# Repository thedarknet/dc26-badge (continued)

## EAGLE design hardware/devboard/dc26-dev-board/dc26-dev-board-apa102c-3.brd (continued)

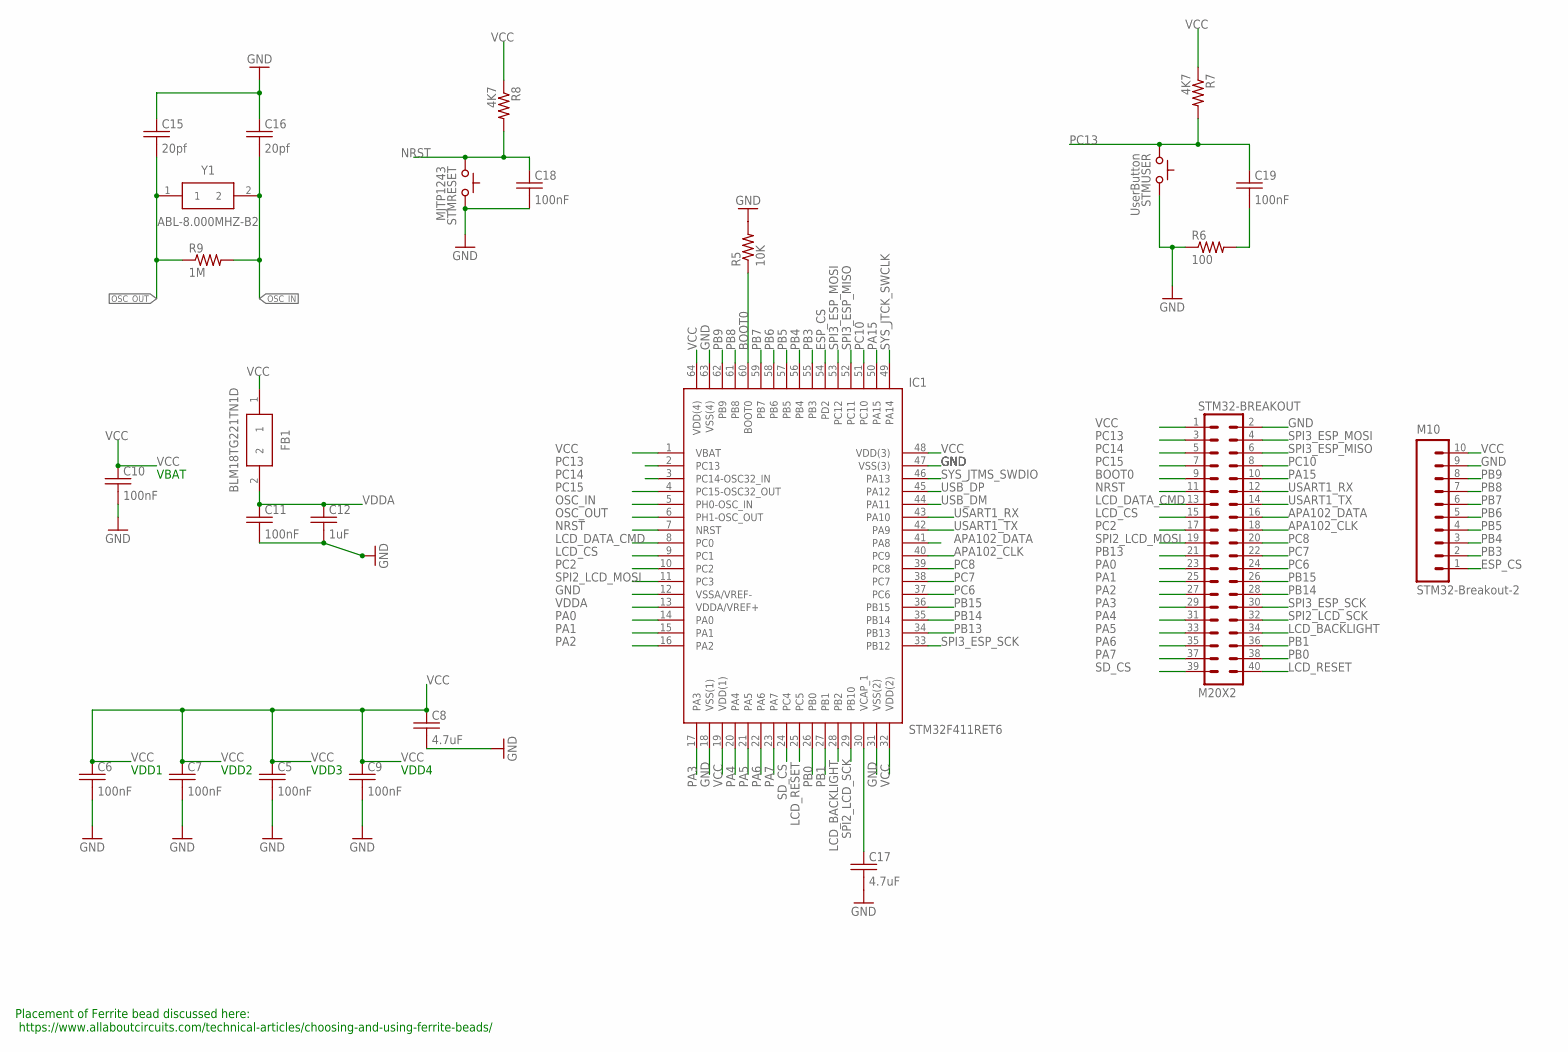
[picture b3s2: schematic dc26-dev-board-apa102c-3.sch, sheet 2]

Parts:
C5, C6, C7, C9, C10, C11, C18, C19: 100nF; C0805
C8, C17: 4.7uF; C0805
C12: 1uF; C0805
C15, C16: 20pf; C0805
FB1: BLM18TG221TN1D; BEADC1608X75N
IC1: STM32F411RET6; QFP50P1200X1200X160-64N
M10: STM32-Breakout-2; 1X10
R5: 10K; 0805
R6: 100; 0805
R7, R8: 4K7; 0805
R9: 1M; 0805
STM32-BREAKOUT: M20X2; 2X20
STMRESET: MJTP1243; TACTILE-2PIN-NARROW
STMUSER: UserButton; TACTILE-2PIN-NARROW
Y1: ABL-8.000MHZ-B2; HC/49US_(AT49)PTH

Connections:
APA102_CLK: IC1.40 (PC9), STM32-BREAKOUT.18; also elsewhere on the board
APA102_DATA: IC1.41 (PA8), STM32-BREAKOUT.16; also elsewhere on the board
BOOT0: IC1.60 (BOOT0), R5.1, STM32-BREAKOUT.9
ESP_CS: IC1.54 (PD2), M10.1; also elsewhere on the board
GND: C5.2, C6.2, C7.2, C8.2, C9.2, C10.2, C11.2, C12.2, C15.1, C16.1, C17.2, C18.2, IC1.12 (VSSA/VREF-), IC1.18 (VSS(1)), IC1.31 (VSS(2)), IC1.47 (VSS(3)), IC1.63 (VSS(4)), M10.9, R5.2, R6.1, STM32-BREAKOUT.2, STMRESET.P$1 (A), STMUSER.P$1 (A); also elsewhere on the board
LCD_BACKLIGHT: IC1.28 (PB2), STM32-BREAKOUT.34; also elsewhere on the board
LCD_CS: IC1.9 (PC1), STM32-BREAKOUT.15; also elsewhere on the board
LCD_DATA_CMD: IC1.8 (PC0), STM32-BREAKOUT.13; also elsewhere on the board
LCD_RESET: IC1.25 (PC5), STM32-BREAKOUT.40; also elsewhere on the board
unnamed: C19.2, R6.2
unnamed: C17.1, IC1.30 (VCAP_1)
NRST: C18.1, IC1.7 (NRST), R8.2, STM32-BREAKOUT.11, STMRESET.P$2 (C)
OSC_IN: C16.2, IC1.5 (PH0-OSC_IN), R9.2, Y1.2
OSC_OUT: C15.2, IC1.6 (PH1-OSC_OUT), R9.1, Y1.1
PA0: IC1.14 (PA0), STM32-BREAKOUT.23
PA1: IC1.15 (PA1), STM32-BREAKOUT.25
PA2: IC1.16 (PA2), STM32-BREAKOUT.27
PA3: IC1.17 (PA3), STM32-BREAKOUT.29
PA4: IC1.20 (PA4), STM32-BREAKOUT.31
PA5: IC1.21 (PA5), STM32-BREAKOUT.33
PA6: IC1.22 (PA6), STM32-BREAKOUT.35
PA7: IC1.23 (PA7), STM32-BREAKOUT.37
PA15: IC1.50 (PA15), STM32-BREAKOUT.10
PB0: IC1.26 (PB0), STM32-BREAKOUT.38
PB1: IC1.27 (PB1), STM32-BREAKOUT.36
PB3: IC1.55 (PB3), M10.2
PB4: IC1.56 (PB4), M10.3
PB5: IC1.57 (PB5), M10.4
PB6: IC1.58 (PB6), M10.5
PB7: IC1.59 (PB7), M10.6
PB8: IC1.61 (PB8), M10.7
PB9: IC1.62 (PB9), M10.8
PB13: IC1.34 (PB13), STM32-BREAKOUT.21
PB14: IC1.35 (PB14), STM32-BREAKOUT.28
PB15: IC1.36 (PB15), STM32-BREAKOUT.26
PC2: IC1.10 (PC2), STM32-BREAKOUT.17
PC6: IC1.37 (PC6), STM32-BREAKOUT.24
PC7: IC1.38 (PC7), STM32-BREAKOUT.22
PC8: IC1.39 (PC8), STM32-BREAKOUT.20
PC10: IC1.51 (PC10), STM32-BREAKOUT.8
PC13: C19.1, IC1.2 (PC13), R7.2, STM32-BREAKOUT.3, STMUSER.P$2 (C)
PC14: IC1.3 (PC14-OSC32_IN), STM32-BREAKOUT.5
PC15: IC1.4 (PC15-OSC32_OUT), STM32-BREAKOUT.7
SD_CS: IC1.24 (PC4), STM32-BREAKOUT.39; also elsewhere on the board
SPI2_LCD_MOSI: IC1.11 (PC3), STM32-BREAKOUT.19; also elsewhere on the board
SPI2_LCD_SCK: IC1.29 (PB10), STM32-BREAKOUT.32; also elsewhere on the board
SPI3_ESP_MISO: IC1.52 (PC11), STM32-BREAKOUT.6; also elsewhere on the board
SPI3_ESP_MOSI: IC1.53 (PC12), STM32-BREAKOUT.4; also elsewhere on the board
SPI3_ESP_SCK: IC1.33 (PB12), STM32-BREAKOUT.30; also elsewhere on the board
SYS_JTCK_SWCLK: IC1.49 (PA14); also elsewhere on the board
SYS_JTMS_SWDIO: IC1.46 (PA13); also elsewhere on the board
USART1_RX: IC1.43 (PA10), STM32-BREAKOUT.12
USART1_TX: IC1.42 (PA9), STM32-BREAKOUT.14
USB_DM: IC1.44 (PA11); also elsewhere on the board
USB_DP: IC1.45 (PA12); also elsewhere on the board
VCC: C5.1, C6.1, C7.1, C8.1, C9.1, C10.1, FB1.1, IC1.1 (VBAT), IC1.19 (VDD(1)), IC1.32 (VDD(2)), IC1.48 (VDD(3)), IC1.64 (VDD(4)), M10.10, R7.1, R8.1, STM32-BREAKOUT.1; also elsewhere on the board
VDDA: C11.1, C12.1, FB1.2, IC1.13 (VDDA/VREF+)

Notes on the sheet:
Placement of Ferrite bead discussed here: https://www.allaboutcircuits.com/technical-articles/choosing-and-using-ferrite-beads/
VBAT
VDD1
VDD2
VDD3
VDD4

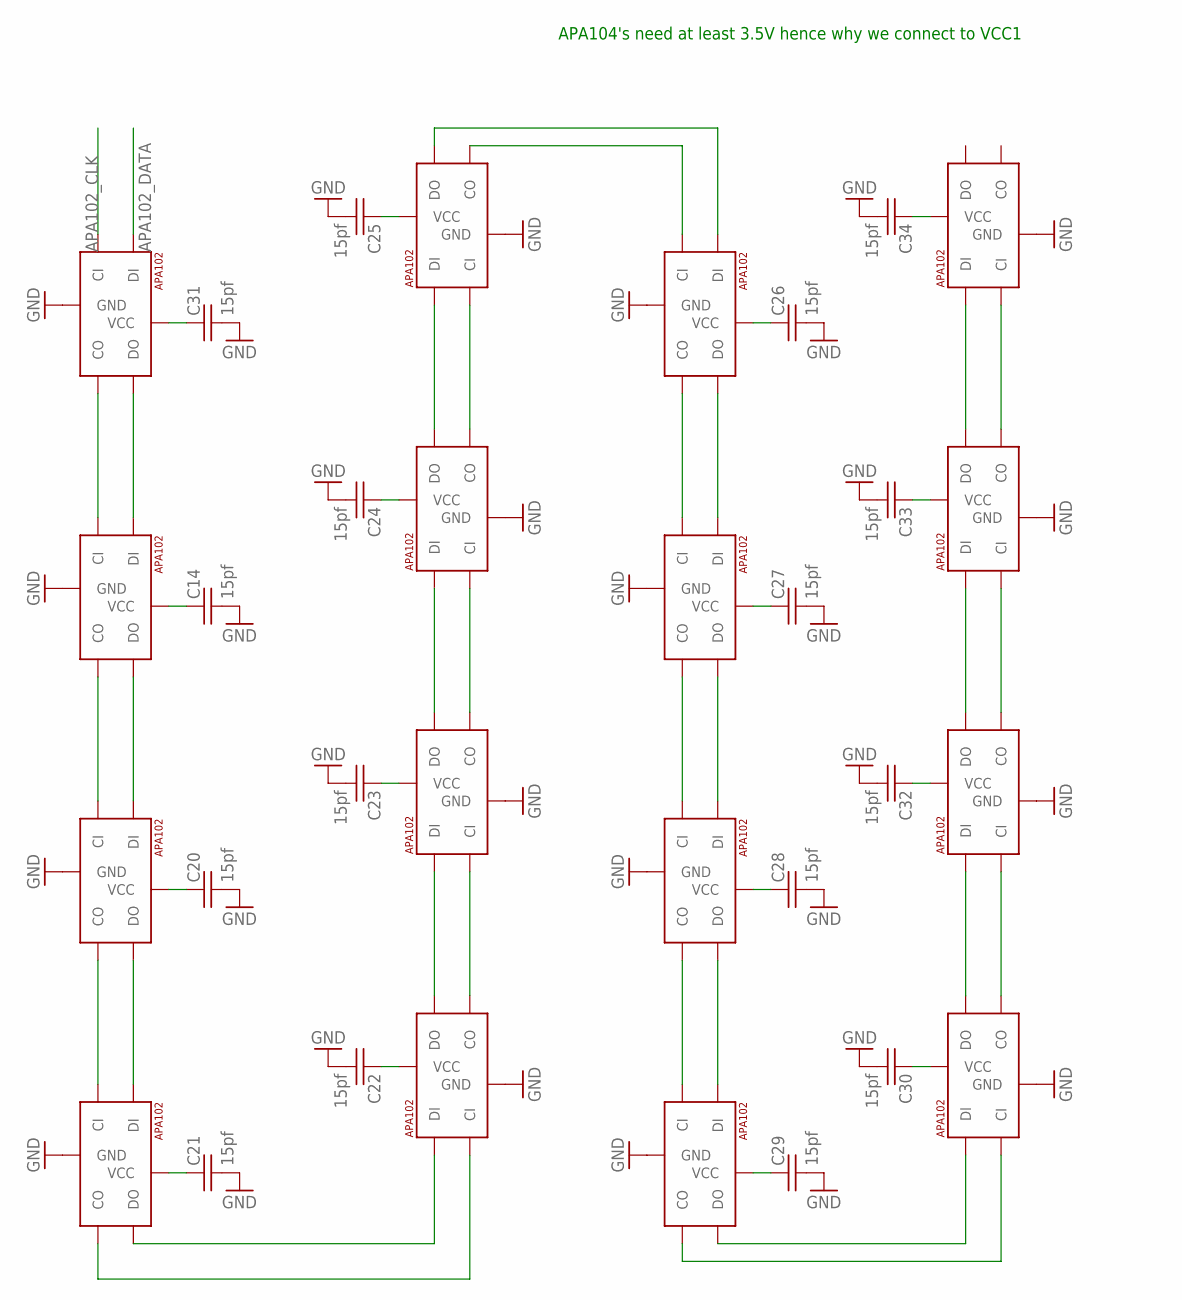
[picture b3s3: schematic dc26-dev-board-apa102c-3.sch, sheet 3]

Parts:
C14, C20, C21, C22, C23, C24, C25, C26, C27, C28, C29, C30, C31, C32, C33, C34: 15pf; C0805
U$5, U$6, U$7, U$8, U$9, U$10, U$11, U$12, U$13, U$14, U$15, U$16, U$17, U$18, U$19, U$20: APA1025050; APA102_5050

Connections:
APA102_CLK: U$8.5 (CI); also elsewhere on the board
APA102_DATA: U$8.4 (DI); also elsewhere on the board
GND: C14.2, C20.2, C21.2, C22.2, C23.2, C24.2, C25.2, C26.2, C27.2, C28.2, C29.2, C30.2, C31.2, C32.2, C33.2, C34.2, U$5.6 (GND), U$6.6 (GND), U$7.6 (GND), U$8.6 (GND), U$9.6 (GND), U$10.6 (GND), U$11.6 (GND), U$12.6 (GND), U$13.6 (GND), U$14.6 (GND), U$15.6 (GND), U$16.6 (GND), U$17.6 (GND), U$18.6 (GND), U$19.6 (GND), U$20.6 (GND); also elsewhere on the board
unnamed: U$5.5 (CI), U$8.2 (CO)
unnamed: U$5.2 (CO), U$6.5 (CI)
unnamed: U$6.2 (CO), U$7.5 (CI)
unnamed: U$6.3 (DO), U$7.4 (DI)
unnamed: U$5.3 (DO), U$6.4 (DI)
unnamed: U$5.4 (DI), U$8.3 (DO)
unnamed: U$7.3 (DO), U$9.4 (DI)
unnamed: U$7.2 (CO), U$9.5 (CI)
unnamed: U$9.2 (CO), U$10.5 (CI)
unnamed: U$9.3 (DO), U$10.4 (DI)
unnamed: U$10.2 (CO), U$11.5 (CI)
unnamed: U$10.3 (DO), U$11.4 (DI)
unnamed: U$11.2 (CO), U$12.5 (CI)
unnamed: U$11.3 (DO), U$12.4 (DI)
unnamed: U$12.2 (CO), U$13.5 (CI)
unnamed: U$12.3 (DO), U$13.4 (DI)
unnamed: U$13.2 (CO), U$14.5 (CI)
unnamed: U$13.3 (DO), U$14.4 (DI)
unnamed: U$14.2 (CO), U$15.5 (CI)
unnamed: U$14.3 (DO), U$15.4 (DI)
unnamed: U$15.2 (CO), U$16.5 (CI)
unnamed: U$15.3 (DO), U$16.4 (DI)
unnamed: U$16.3 (DO), U$17.4 (DI)
unnamed: U$16.2 (CO), U$17.5 (CI)
unnamed: U$17.3 (DO), U$18.4 (DI)
unnamed: U$17.2 (CO), U$18.5 (CI)
unnamed: U$18.2 (CO), U$19.5 (CI)
unnamed: U$18.3 (DO), U$19.4 (DI)
unnamed: U$19.2 (CO), U$20.5 (CI)
unnamed: U$19.3 (DO), U$20.4 (DI)
VIN: C14.1, C20.1, C21.1, C22.1, C23.1, C24.1, C25.1, C26.1, C27.1, C28.1, C29.1, C30.1, C31.1, C32.1, C33.1, C34.1, U$5.1 (VCC), U$6.1 (VCC), U$7.1 (VCC), U$8.1 (VCC), U$9.1 (VCC), U$10.1 (VCC), U$11.1 (VCC), U$12.1 (VCC), U$13.1 (VCC), U$14.1 (VCC), U$15.1 (VCC), U$16.1 (VCC), U$17.1 (VCC), U$18.1 (VCC), U$19.1 (VCC), U$20.1 (VCC); also elsewhere on the board

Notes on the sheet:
APA104's need at least 3.5V hence why we connect to VCC1

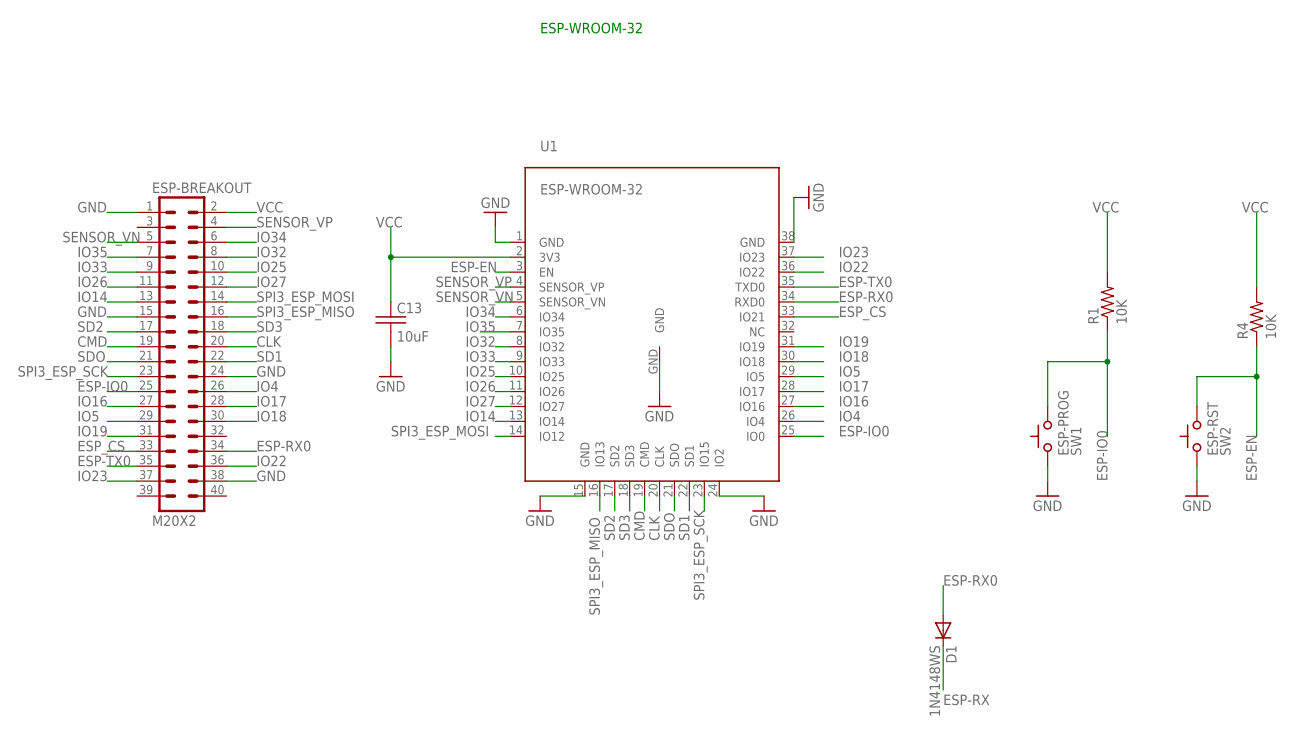
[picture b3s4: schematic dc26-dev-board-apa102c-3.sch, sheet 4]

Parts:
C13: 10uF; C0805
D1: 1N4148WS; SOD-323
ESP-BREAKOUT: M20X2; 2X20
ESP-PROG: SW1; TACTILE-2PIN-NARROW
ESP-RST: SW2; TACTILE-2PIN-NARROW
R1, R4: 10K; 0805
U1: ESP-WROOM-32

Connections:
CLK: ESP-BREAKOUT.20, U1.20 (CLK)
CMD: ESP-BREAKOUT.19, U1.19 (CMD)
ESP-EN: ESP-RST.P$1 (A), R4.1, U1.3 (EN)
ESP-IO0: ESP-BREAKOUT.25, ESP-PROG.P$1 (A), R1.1, U1.25 (IO0)
ESP-RX: D1.1 (C); also elsewhere on the board
ESP-RX0: D1.2 (A), ESP-BREAKOUT.34, U1.34 (RXD0)
ESP-TX0: ESP-BREAKOUT.35, U1.35 (TXD0); also elsewhere on the board
ESP_CS: ESP-BREAKOUT.33, U1.33 (IO21); also elsewhere on the board
GND: C13.2, ESP-BREAKOUT.1, ESP-BREAKOUT.15, ESP-BREAKOUT.24, ESP-BREAKOUT.38, ESP-PROG.P$2 (C), ESP-RST.P$2 (C), U1.1 (GND), U1.15 (GND), U1.24 (IO2), U1.38 (GND), U1.GND; also elsewhere on the board
IO4: ESP-BREAKOUT.26, U1.26 (IO4)
IO5: ESP-BREAKOUT.29, U1.29 (IO5)
IO14: ESP-BREAKOUT.13, U1.13 (IO14)
IO16: ESP-BREAKOUT.27, U1.27 (IO16)
IO17: ESP-BREAKOUT.28, U1.28 (IO17)
IO18: ESP-BREAKOUT.30, U1.30 (IO18)
IO19: ESP-BREAKOUT.31, U1.31 (IO19)
IO22: ESP-BREAKOUT.36, U1.36 (IO22)
IO23: ESP-BREAKOUT.37, U1.37 (IO23)
IO25: ESP-BREAKOUT.10, U1.10 (IO25)
IO26: ESP-BREAKOUT.11, U1.11 (IO26)
IO27: ESP-BREAKOUT.12, U1.12 (IO27)
IO32: ESP-BREAKOUT.8, U1.8 (IO32)
IO33: ESP-BREAKOUT.9, U1.9 (IO33)
IO34: ESP-BREAKOUT.6, U1.6 (IO34)
IO35: ESP-BREAKOUT.7, U1.7 (IO35)
SD1: ESP-BREAKOUT.22, U1.22 (SD1)
SD2: ESP-BREAKOUT.17, U1.17 (SD2)
SD3: ESP-BREAKOUT.18, U1.18 (SD3)
SDO: ESP-BREAKOUT.21, U1.21 (SDO)
SENSOR_VN: ESP-BREAKOUT.5, U1.5 (SENSOR_VN)
SENSOR_VP: ESP-BREAKOUT.4, U1.4 (SENSOR_VP)
SPI3_ESP_MISO: ESP-BREAKOUT.16, U1.16 (IO13); also elsewhere on the board
SPI3_ESP_MOSI: ESP-BREAKOUT.14, U1.14 (IO12); also elsewhere on the board
SPI3_ESP_SCK: ESP-BREAKOUT.23, U1.23 (IO15); also elsewhere on the board
VCC: C13.1, ESP-BREAKOUT.2, R1.2, R4.2, U1.2 (3V3); also elsewhere on the board

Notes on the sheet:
ESP-WROOM-32

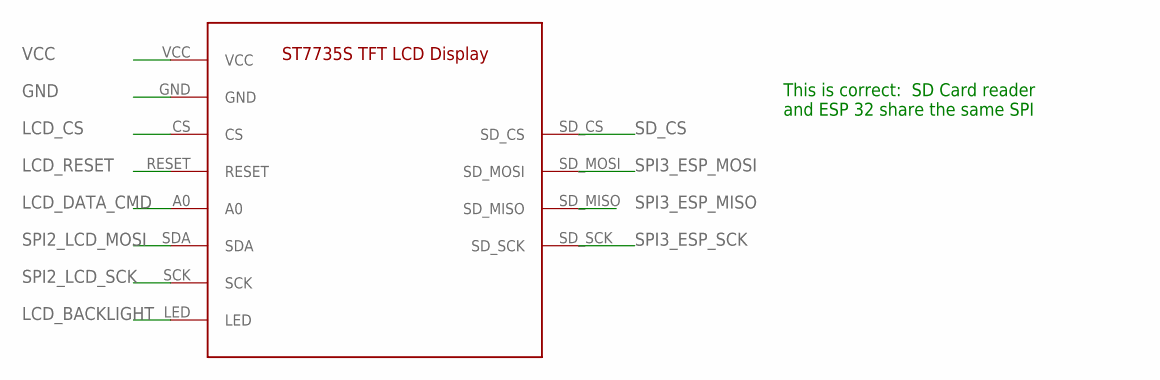
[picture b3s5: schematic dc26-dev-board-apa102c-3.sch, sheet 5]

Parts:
U$1: ST7735S_LCD_MODULE; ST7735S_LCD_DISPLAY

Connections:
GND: U$1.GND; also elsewhere on the board
LCD_BACKLIGHT: U$1.LED; also elsewhere on the board
LCD_CS: U$1.CS; also elsewhere on the board
LCD_DATA_CMD: U$1.A0; also elsewhere on the board
LCD_RESET: U$1.RESET; also elsewhere on the board
SD_CS: U$1.SD_CS; also elsewhere on the board
SPI2_LCD_MOSI: U$1.SDA; also elsewhere on the board
SPI2_LCD_SCK: U$1.SCK; also elsewhere on the board
SPI3_ESP_MISO: U$1.SD_MISO; also elsewhere on the board
SPI3_ESP_MOSI: U$1.SD_MOSI; also elsewhere on the board
SPI3_ESP_SCK: U$1.SD_SCK; also elsewhere on the board
VCC: U$1.VCC; also elsewhere on the board

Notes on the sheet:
This is correct: SD Card reader and ESP 32 share the same SPI

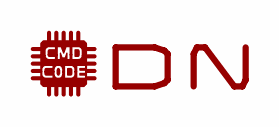
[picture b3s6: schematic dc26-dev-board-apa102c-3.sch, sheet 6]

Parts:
U$2: CMD_C0DE_LOGO
U$3: DARKNET_DD; DARKNET_D
U$4: DARKNET_NN; DARKNET_N

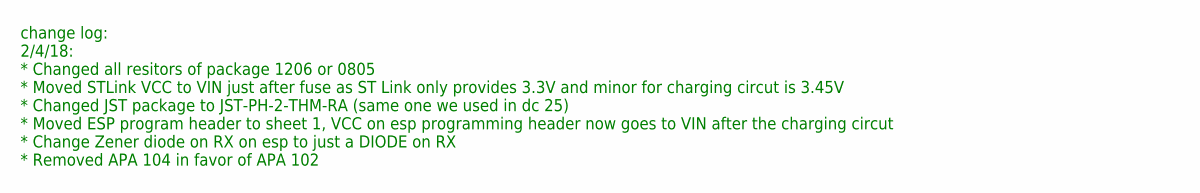
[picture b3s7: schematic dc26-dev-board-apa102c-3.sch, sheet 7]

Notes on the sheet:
change log: 2/4/18: * Changed all resitors of package 1206 or 0805 * Moved STLink VCC to VIN just after fuse as ST Link only provides 3.3V and minor for charging circut is 3.45V * Changed JST package to JST-PH-2-THM-RA (same one we used in dc 25) * Moved ESP program header to sheet 1, VCC on esp pr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

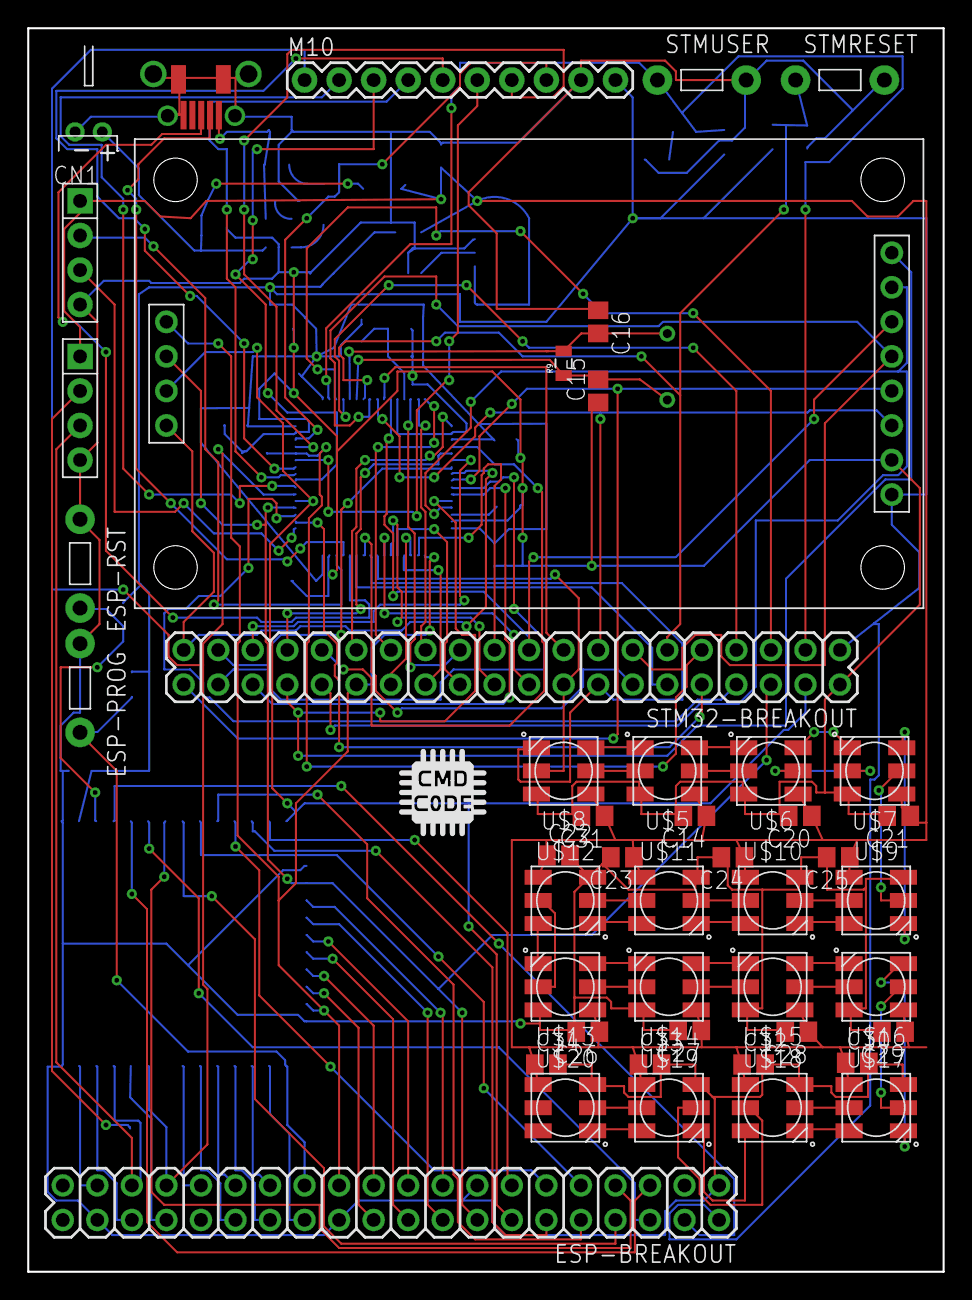
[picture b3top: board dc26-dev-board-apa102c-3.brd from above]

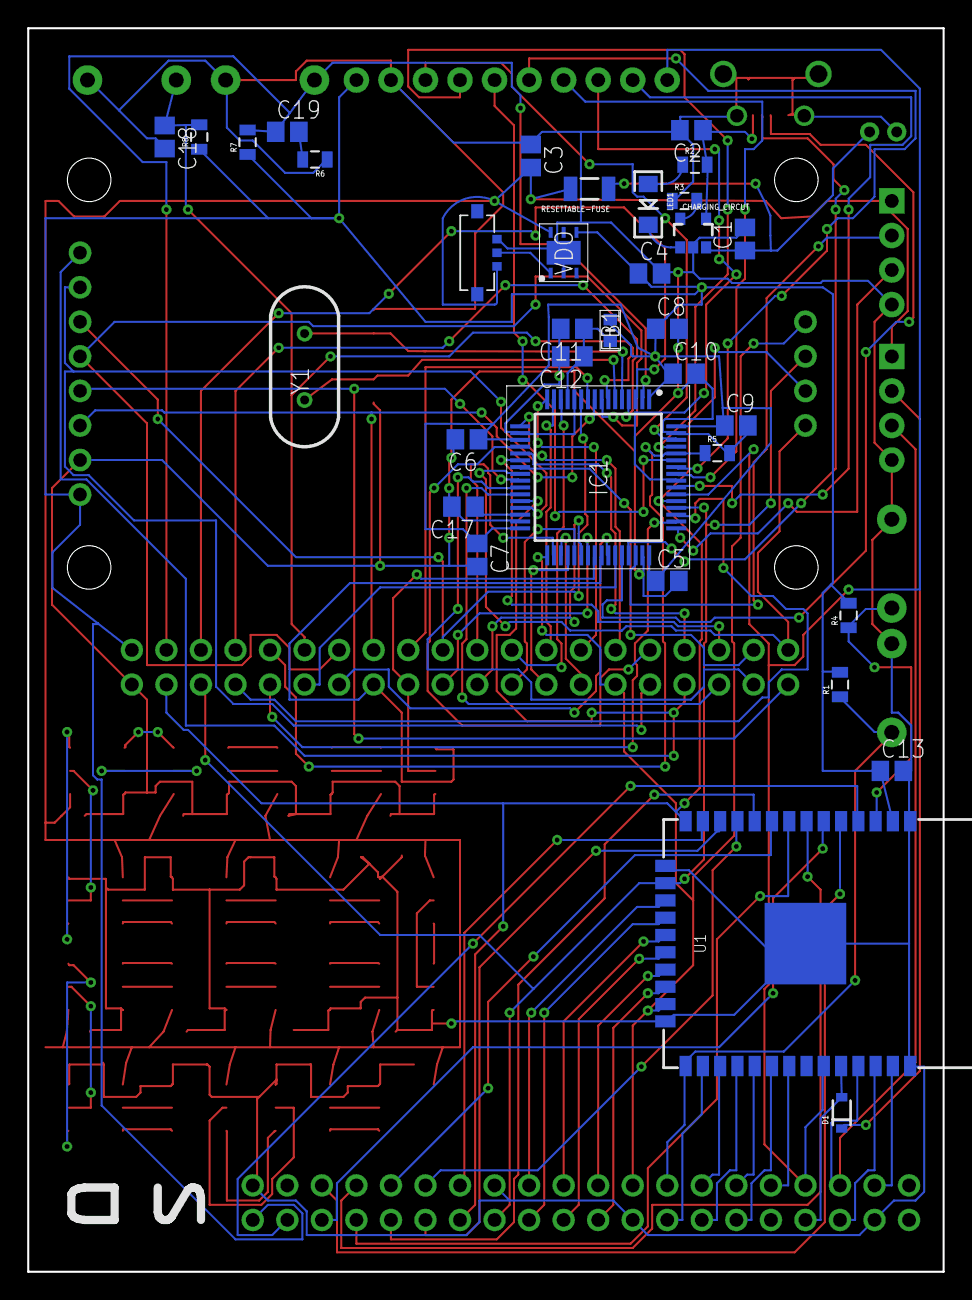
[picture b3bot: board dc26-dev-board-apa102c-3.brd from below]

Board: 2 copper layers, 67.3 x 91.4 mm, 84 parts (34 on the bottom side), 123 nets.

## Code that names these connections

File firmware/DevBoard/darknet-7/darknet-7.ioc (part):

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Mcu.Name=STM32F411R(C-E)Tx
Mcu.Package=LQFP64
Mcu.UserName=STM32F411RETx
PA10.GPIOParameters=GPIO_Label
PA10.GPIO_Label=USART1_RX_TO_ESP_TX_PIN_4
PA10.Mode=Asynchronous
PA10.Signal=USART1_RX
PA11.Mode=Device_Only
PA11.Signal=USB_OTG_FS_DM
PA12.Mode=Device_Only
PA12.Signal=USB_OTG_FS_DP
PA13.Mode=Serial_Wire
PA13.Signal=SYS_JTMS-SWDIO
PA14.Mode=Serial_Wire
PA14.Signal=SYS_JTCK-SWCLK
PA2.Mode=Asynchronous
PA2.Signal=USART2_TX
PA3.Mode=Asynchronous
PA3.Signal=USART2_RX
PA8.GPIOParameters=GPIO_Label
PA8.GPIO_Label=SHITTY_ADD_ON_BADGE_I2C_SCL
PA8.Mode=I2C
PA8.Signal=I2C3_SCL
PA9.GPIOParameters=GPIO_Label
PA9.GPIO_Label=USART1_TX_TO_ESP_RX_PIN_5
PA9.Mode=Asynchronous
PA9.Signal=USART1_TX
PB10.GPIOParameters=GPIO_Label
PB10.GPIO_Label=SPI2_LCD_SCK
PB10.Mode=Simplex_Bidirectional_Master
PB10.Signal=SPI2_SCK
PB12.GPIOParameters=GPIO_Label
PB12.GPIO_Label=SPI3_SD_SCK
PB12.Mode=Full_Duplex_Master
PB12.Signal=SPI3_SCK
PB2.GPIOParameters=GPIO_Label
PB2.GPIO_Label=LCD_BACKLIGHT
PB2.Signal=GPIO_Output
PB4.GPIOParameters=GPIO_Label
PB4.GPIO_Label=SHITTY_ADD_ON_BADGE_I2C_SDA
PB4.Mode=I2C
PB4.Signal=I2C3_SDA
PB6.GPIOParameters=GPIO_Label
PB6.GPIO_Label=ESP_I2C1_SCL
PB6.Mode=I2C
PB6.Signal=I2C1_SCL
PB7.GPIOParameters=GPIO_Label
PB7.GPIO_Label=ESP_I2C1_SDA
PB7.Mode=I2C
PB7.Signal=I2C1_SDA
PB8.GPIOParameters=GPIO_Label
PB8.GPIO_Label=BUTTON_UP
PB8.Signal=GPIO_Input
PB9.GPIOParameters=GPIO_Label
PB9.GPIO_Label=BUTTON_DOWN
PB9.Signal=GPIO_Input
PC0.GPIOParameters=GPIO_Label
PC0.GPIO_Label=LCD_DATA_CMD
PC0.Signal=GPIO_Output
PC1.GPIOParameters=GPIO_Label
PC1.GPIO_Label=LCD_CS
PC1.Signal=GPIO_Output
PC10.GPIOParameters=GPIO_Label
PC10.GPIO_Label=SIMPLE_LED1
PC10.Signal=GPIO_Output
PC11.GPIOParameters=GPIO_Label
PC11.GPIO_Label=SPI3_SD_MISO
PC11.Mode=Full_Duplex_Master
PC11.Signal=SPI3_MISO
PC12.GPIOParameters=GPIO_Label
PC12.GPIO_Label=SPI3_SD_MOSI
PC12.Mode=Full_Duplex_Master
PC12.Signal=SPI3_MOSI
PC13-ANTI_TAMP.GPIOParameters=GPIO_Label
PC13-ANTI_TAMP.GPIO_Label=MID_BUTTON1
PC13-ANTI_TAMP.Signal=GPIO_Input
PC14-OSC32_IN.GPIOParameters=GPIO_Label
PC14-OSC32_IN.GPIO_Label=BUTTON_RIGHT
PC14-OSC32_IN.Signal=GPIO_Input
PC15-OSC32_OUT.GPIOParameters=GPIO_Label
PC15-OSC32_OUT.GPIO_Label=BUTTON_FIRE1
PC15-OSC32_OUT.Signal=GPIO_Input
PC2.GPIOParameters=GPIO_Label
PC2.GPIO_Label=BUTTON_LEFT
PC2.Signal=GPIO_Input
PC3.GPIOParameters=GPIO_Label
PC3.GPIO_Label=SPI2_LCD_MOSI
PC3.Mode=Simplex_Bidirectional_Master
PC3.Signal=SPI2_MOSI
PC4.GPIOParameters=GPIO_Label
PC4.GPIO_Label=SD_CS
PC4.Signal=GPIO_Output
PC5.GPIOParameters=GPIO_Label
PC5.GPIO_Label=LCD_RESET
PC5.Signal=GPIO_Output
PC7.GPIOParameters=GPIO_Speed,GPIO_Label
PC7.GPIO_Label=GPIO_APA106_DATA
PC7.GPIO_Speed=GPIO_SPEED_FREQ_MEDIUM
PC7.Signal=GPIO_Output
PC8.GPIOParameters=GPIO_Label
PC8.GPIO_Label=GPIO_APA102_DATA
PC8.Signal=GPIO_Output
PC9.GPIOParameters=GPIO_Speed,GPIO_PuPd,GPIO_Label
PC9.GPIO_Label=TIM_APA102_CLK
PC9.GPIO_PuPd=GPIO_PULLUP
PC9.GPIO_Speed=GPIO_SPEED_FREQ_HIGH
PC9.Signal=S_TIM3_CH4
PD2.GPIOParameters=GPIO_Label
PD2.GPIO_Label=ESP_INTER
PD2.Signal=GPXTI2
PH0\ -\ OSC_IN.Mode=HSE-External-Oscillator
PH0\ -\ OSC_IN.Signal=RCC_OSC_IN
PH1\ -\ OSC_OUT.Mode=HSE-External-Oscillator
PH1\ -\ OSC_OUT.Signal=RCC_OSC_OUT
RCC.HSE_VALUE=8000000
RCC.SYSCLKFreq_VALUE=96000000.00000001
RCC.SYSCLKSource=RCC_SYSCLKSOURCE_PLLCLK
board=darknet-7

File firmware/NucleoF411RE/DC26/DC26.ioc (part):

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Mcu.Name=STM32F411R(C-E)Tx
Mcu.Package=LQFP64
Mcu.UserName=STM32F411RETx
PA10.Mode=Asynchronous
PA10.Signal=USART1_RX
PA11.Mode=Device_Only
PA11.Signal=USB_OTG_FS_DM
PA12.Mode=Device_Only
PA12.Signal=USB_OTG_FS_DP
PA13.GPIOParameters=GPIO_Label
PA13.GPIO_Label=TMS
PA13.Mode=Serial_Wire
PA13.Signal=SYS_JTMS-SWDIO
PA14.GPIOParameters=GPIO_Label
PA14.GPIO_Label=TCK
PA14.Mode=Serial_Wire
PA14.Signal=SYS_JTCK-SWCLK
PA2.GPIOParameters=GPIO_Label
PA2.GPIO_Label=USART_TX
PA2.Signal=USART2_TX
PA3.GPIOParameters=GPIO_Label
PA3.GPIO_Label=USART_RX
PA3.Signal=USART2_RX
PA5.GPIOParameters=GPIO_Label
PA5.GPIO_Label=LD2 [Green Led]
PA5.Signal=GPIO_Output
PA9.Mode=Asynchronous
PA9.Signal=USART1_TX
PB10.GPIOParameters=GPIO_Label
PB10.GPIO_Label=SPI2_LCD_SCK
PB10.Mode=Simplex_Bidirectional_Master
PB10.Signal=SPI2_SCK
PB12.GPIOParameters=GPIO_Label
PB12.GPIO_Label=SPI3_ESP_SCK
PB12.Mode=Full_Duplex_Master
PB12.Signal=SPI3_SCK
PB2.GPIOParameters=GPIO_Label
PB2.GPIO_Label=LCD_BACKLIGHT
PB2.Signal=GPIO_Output
PB3.GPIOParameters=GPIO_Label
PB3.GPIO_Label=SWO
PB3.Signal=SYS_JTDO-SWO
PB6.Mode=I2C
PB6.Signal=I2C1_SCL
PB7.Mode=I2C
PB7.Signal=I2C1_SDA
PC0.GPIOParameters=GPIO_Label
PC0.GPIO_Label=LCD_DATA_CMD
PC0.Signal=GPIO_Output
PC1.GPIOParameters=GPIO_Label
PC1.GPIO_Label=LCD_CS
PC1.Signal=GPIO_Output
PC11.GPIOParameters=GPIO_Label
PC11.GPIO_Label=SPI3_ESP_MISO
PC11.Mode=Full_Duplex_Master
PC11.Signal=SPI3_MISO
PC12.GPIOParameters=GPIO_Label
PC12.GPIO_Label=SPI3_ESP_MOSI
PC12.Mode=Full_Duplex_Master
PC12.Signal=SPI3_MOSI
PC13-ANTI_TAMP.GPIOParameters=GPIO_Label,GPIO_ModeDefaultEXTI
PC13-ANTI_TAMP.GPIO_Label=B1 [Blue PushButton]
PC13-ANTI_TAMP.GPIO_ModeDefaultEXTI=GPIO_MODE_IT_FALLING
PC13-ANTI_TAMP.Signal=GPXTI13
PC14-OSC32_IN.Signal=RCC_OSC32_IN
PC15-OSC32_OUT.Signal=RCC_OSC32_OUT
PC3.GPIOParameters=GPIO_Label
PC3.GPIO_Label=SPI2_LCD_MOSI
PC3.Mode=Simplex_Bidirectional_Master
PC3.Signal=SPI2_MOSI
PC4.GPIOParameters=GPIO_Label
PC4.GPIO_Label=SD_CS
PC4.Signal=GPIO_Output
PC5.GPIOParameters=GPIO_Label
PC5.GPIO_Label=LCD_RESET
PC5.Signal=GPIO_Output
PC8.GPIOParameters=GPIO_Speed,GPIO_Label
PC8.GPIO_Label=GPIO_APA104_DATA
PC8.GPIO_Speed=GPIO_SPEED_FREQ_HIGH
PC8.Signal=GPIO_Output
PD2.GPIOParameters=GPIO_Speed,PinState,GPIO_Label
PD2.GPIO_Label=ESP_CS
PD2.GPIO_Speed=GPIO_SPEED_FREQ_MEDIUM
PD2.PinState=GPIO_PIN_RESET
PD2.Signal=GPIO_Output
PH0\ -\ OSC_IN.Mode=HSE-External-Oscillator
PH0\ -\ OSC_IN.Signal=RCC_OSC_IN
PH1\ -\ OSC_OUT.Mode=HSE-External-Oscillator
PH1\ -\ OSC_OUT.Signal=RCC_OSC_OUT
RCC.HSE_VALUE=8000000
RCC.SYSCLKFreq_VALUE=96000000.00000001
RCC.SYSCLKSource=RCC_SYSCLKSOURCE_PLLCLK
board=NUCLEO-F411RE
boardIOC=true

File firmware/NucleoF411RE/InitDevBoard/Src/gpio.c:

/**
  ******************************************************************************
  * File Name          : gpio.c
  * Description        : This file provides code for the configuration
  *                      of all used GPIO pins.
  ******************************************************************************
  * This notice applies to any and all portions of this file
  * that are not between comment pairs USER CODE BEGIN and
  * USER CODE END. Other portions of this file, whether 
  * inserted by the user or by software development tools
  * are owned by their respective copyright owners.
  *
  * Copyright (c) 2017 STMicroelectronics International N.V. 
  * All rights reserved.
  *
  * Redistribution and use in source and binary forms, with or without 
  * modification, are permitted, provided that the following conditions are met:
  *
  * 1. Redistribution of source code must retain the above copyright notice, 
  *    this list of conditions and the following disclaimer.
  * 2. Redistributions in binary form must reproduce the above copyright notice,
  *    this list of conditions and the following disclaimer in the documentation
  *    and/or other materials provided with the distribution.
  * 3. Neither the name of STMicroelectronics nor the names of other 
  *    contributors to this software may be used to endorse or promote products 
  *    derived from this software without specific written permission.
  * 4. This software, including modifications and/or derivative works of this 
  *    software, must execute solely and exclusively on microcontroller or
  *    microprocessor devices manufactured by or for STMicroelectronics.
  * 5. Redistribution and use of this software other than as permitted under 
  *    this license is void and will automatically terminate your rights under 
  *    this license. 
  *
  * THIS SOFTWARE IS PROVIDED BY STMICROELECTRONICS AND CONTRIBUTORS "AS IS" 
  * AND ANY EXPRESS, IMPLIED OR STATUTORY WARRANTIES, INCLUDING, BUT NOT 
  * LIMITED TO, THE IMPLIED WARRANTIES OF MERCHANTABILITY, FITNESS FOR A 
  * PARTICULAR PURPOSE AND NON-INFRINGEMENT OF THIRD PARTY INTELLECTUAL PROPERTY
  * RIGHTS ARE DISCLAIMED TO THE FULLEST EXTENT PERMITTED BY LAW. IN NO EVENT 
  * SHALL STMICROELECTRONICS OR CONTRIBUTORS BE LIABLE FOR ANY DIRECT, INDIRECT,
  * INCIDENTAL, SPECIAL, EXEMPLARY, OR CONSEQUENTIAL DAMAGES (INCLUDING, BUT NOT
  * LIMITED TO, PROCUREMENT OF SUBSTITUTE GOODS OR SERVICES; LOSS OF USE, DATA, 
  * OR PROFITS; OR BUSINESS INTERRUPTION) HOWEVER CAUSED AND ON ANY THEORY OF 
  * LIABILITY, WHETHER IN CONTRACT, STRICT LIABILITY, OR TORT (INCLUDING 
  * NEGLIGENCE OR OTHERWISE) ARISING IN ANY WAY OUT OF THE USE OF THIS SOFTWARE,
  * EVEN IF ADVISED OF THE POSSIBILITY OF SUCH DAMAGE.
  *
  ******************************************************************************
  */

/* Includes ------------------------------------------------------------------*/
#include "gpio.h"
/* USER CODE BEGIN 0 */

/* USER CODE END 0 */

/*----------------------------------------------------------------------------*/
/* Configure GPIO                                                             */
/*----------------------------------------------------------------------------*/
/* USER CODE BEGIN 1 */

/* USER CODE END 1 */

/** Configure pins as 
        * Analog 
        * Input 
        * Output
        * EVENT_OUT
        * EXTI
        * Free pins are configured automatically as Analog (this feature is enabled through 
        * the Code Generation settings)
     PA2   ------> USART2_TX
     PA3   ------> USART2_RX
*/
void MX_GPIO_Init(void)
{

  GPIO_InitTypeDef GPIO_InitStruct;

  /* GPIO Ports Clock Enable */
  __HAL_RCC_GPIOC_CLK_ENABLE();
  __HAL_RCC_GPIOH_CLK_ENABLE();
  __HAL_RCC_GPIOA_CLK_ENABLE();
  __HAL_RCC_GPIOB_CLK_ENABLE();
  __HAL_RCC_GPIOD_CLK_ENABLE();

  /*Configure GPIO pin Output Level */
  HAL_GPIO_WritePin(LCD_CS_GPIO_Port, LCD_CS_Pin, GPIO_PIN_RESET);

  /*Configure GPIO pin Output Level */
  HAL_GPIO_WritePin(LD2_GPIO_Port, LD2_Pin, GPIO_PIN_RESET);

  /*Configure GPIO pin Output Level */
  HAL_GPIO_WritePin(ESP_CS_GPIO_Port, ESP_CS_Pin, GPIO_PIN_RESET);

  /*Configure GPIO pin : PtPin */
  GPIO_InitStruct.Pin = B1_Pin;
  GPIO_InitStruct.Mode = GPIO_MODE_IT_FALLING;
  GPIO_InitStruct.Pull = GPIO_NOPULL;
  HAL_GPIO_Init(B1_GPIO_Port, &GPIO_InitStruct);

  /*Configure GPIO pins : PC0 PC2 PC4 PC5 
                           PC6 PC7 PC8 PC9 
                           PC10 */
  GPIO_InitStruct.Pin = GPIO_PIN_0|GPIO_PIN_2|GPIO_PIN_4|GPIO_PIN_5 
                          |GPIO_PIN_6|GPIO_PIN_7|GPIO_PIN_8|GPIO_PIN_9 
                          |GPIO_PIN_10;
  GPIO_InitStruct.Mode = GPIO_MODE_ANALOG;
  GPIO_InitStruct.Pull = GPIO_NOPULL;
  HAL_GPIO_Init(GPIOC, &GPIO_InitStruct);

  /*Configure GPIO pin : PtPin */
  GPIO_InitStruct.Pin = LCD_CS_Pin;
  GPIO_InitStruct.Mode = GPIO_MODE_OUTPUT_PP;
  GPIO_InitStruct.Pull = GPIO_NOPULL;
  GPIO_InitStruct.Speed = GPIO_SPEED_FREQ_LOW;
  HAL_GPIO_Init(LCD_CS_GPIO_Port, &GPIO_InitStruct);

  /*Configure GPIO pins : PA0 PA1 PA4 PA6 
                           PA7 PA8 PA15 */
  GPIO_InitStruct.Pin = GPIO_PIN_0|GPIO_PIN_1|GPIO_PIN_4|GPIO_PIN_6 
                          |GPIO_PIN_7|GPIO_PIN_8|GPIO_PIN_15;
  GPIO_InitStruct.Mode = GPIO_MODE_ANALOG;
  GPIO_InitStruct.Pull = GPIO_NOPULL;
  HAL_GPIO_Init(GPIOA, &GPIO_InitStruct);

  /*Configure GPIO pins : PAPin PAPin */
  GPIO_InitStruct.Pin = USART_TX_Pin|USART_RX_Pin;
  GPIO_InitStruct.Mode = GPIO_MODE_AF_PP;
  GPIO_InitStruct.Pull = GPIO_NOPULL;
  GPIO_InitStruct.Speed = GPIO_SPEED_FREQ_VERY_HIGH;
  GPIO_InitStruct.Alternate = GPIO_AF7_USART2;
  HAL_GPIO_Init(GPIOA, &GPIO_InitStruct);

  /*Configure GPIO pin : PtPin */
  GPIO_InitStruct.Pin = LD2_Pin;
  GPIO_InitStruct.Mode = GPIO_MODE_OUTPUT_PP;
  GPIO_InitStruct.Pull = GPIO_NOPULL;
  GPIO_InitStruct.Speed = GPIO_SPEED_FREQ_LOW;
  HAL_GPIO_Init(LD2_GPIO_Port, &GPIO_InitStruct);

  /*Configure GPIO pins : PB0 PB1 PB2 PB13 
                           PB14 PB15 PB4 PB5 
                           PB6 PB7 PB8 PB9 */
  GPIO_InitStruct.Pin = GPIO_PIN_0|GPIO_PIN_1|GPIO_PIN_2|GPIO_PIN_13 
                          |GPIO_PIN_14|GPIO_PIN_15|GPIO_PIN_4|GPIO_PIN_5 
                          |GPIO_PIN_6|GPIO_PIN_7|GPIO_PIN_8|GPIO_PIN_9;
  GPIO_InitStruct.Mode = GPIO_MODE_ANALOG;
  GPIO_InitStruct.Pull = GPIO_NOPULL;
  HAL_GPIO_Init(GPIOB, &GPIO_InitStruct);

  /*Configure GPIO pin : PtPin */
  GPIO_InitStruct.Pin = ESP_CS_Pin;
  GPIO_InitStruct.Mode = GPIO_MODE_OUTPUT_PP;
  GPIO_InitStruct.Pull = GPIO_NOPULL;
  GPIO_InitStruct.Speed = GPIO_SPEED_FREQ_MEDIUM;
  HAL_GPIO_Init(ESP_CS_GPIO_Port, &GPIO_InitStruct);

}

/* USER CODE BEGIN 2 */

/* USER CODE END 2 */

/**
  * @}
  */

/**
  * @}
  */

/************************ (C) COPYRIGHT STMicroelectronics *****END OF FILE****/

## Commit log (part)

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2017-12-03 initial project check in
2017-12-03 added esp sdk and documentation
2017-12-04 stub of things working
2017-12-04 new project
2017-12-04 added i2c
2017-12-07 initial board schema
2017-12-11 WIP for board
2017-12-12 power scheme done?
2017-12-13 more docs, added GPIOs for SD_CS and APA104s scemea farther along
2017-12-20 removing files that don't need to be there
2017-12-22 NFC / RFID docs
2017-12-29 added ferrite bead updated VSS to go to gnd
2017-12-31 all errors gone from schema
2017-12-31 added a user button and a button to reset
2018-01-01 swapped out voltage regulator for one that supports 1A rather than just .5A
2018-01-02 inital board layout
2018-01-02 auto routed boardwith some minor vcc changes by hand.
2018-01-03 minor fixed of part naming and added todo file
2018-01-04 Autoroute (#1)
    * inital board layout
    * first auto route
    * auto routed boardwith some minor vcc changes by hand.
    * minor fixed of part naming and added todo file
    * added R9 to crystal
    moved logo and DN to tslik and bsilk layers
2018-01-04 add debug config file
2018-01-13 updated esp-idf
2018-01-30 adding files
2018-02-08 more updates see last sheet for details
2018-02-11 started routing of devboard2
2018-02-17 power run not but not gpio
2018-02-18 fixed all board errors except air wires
2018-02-18 ran power to apa102
2018-03-17 board sent to oshpark
2018-03-19 Board2 - (#2)
    * initial code compiling for esp32
    * adding files
    * more updates see last sheet for details
    * added apa102
    * started routing of devboard2
    * power run not but not gpio
2018-03-26 updated project to be c++ rather than just c
2018-03-27 adding new ldo
2018-04-09 update esp-idf
2018-04-14 adding initial spi test
2018-04-14 adding more hardware docs
2018-04-16 tried I2C....but even esp-idf example does not work!
2018-04-16 adding uart code
2018-04-17 adding new LDO part
2018-04-18 updated board schema version 3
2018-04-25 dc26-'final' board ready
2018-04-25 logo causing 0 width polys will fix later
2018-04-28 added logo to library added logos to board
2018-04-29 wifi as an AP is now working more work to do but basics is there
2018-04-30 removed extra variable
2018-04-30 updated board
2018-04-30 start working on 3d renderer again
2018-04-30 lcd is working 128x32
2018-05-07 using flat buffers to generate protocol between mcus
2018-05-08 adding the ability to turn on static queue
2018-05-08 adding flatbuffers
2018-05-08 addeding windows binary
2018-05-11 adding files before I add libesphttp as a component
2018-05-12 libesphttp now checked in compiles and works with esp32 build system
2018-05-14 we have a working web server, wifi connection is _REALLY_ slow
2018-05-15 tx send task turne don
2018-05-17 increased the size of the apa106f5 wholes updated ratsnet
2018-05-19 set darknet style adding basic fatfs code base
2018-05-20 Added art work, fixed via drills, and started some initial trace cleanup. Still need to move Cmdc0de/Krux logos into place.
2018-05-20 wip for sd card
2018-05-21 turing off sd card since for some reason the test board will not turn on the clk signal. Not sure if this a software problem or did I do something to the chip when I soliders it on
2018-05-21 clean up of silk screen and artwork
2018-05-21 updated mapping in flash so we can use 32K for settings and contacts and the last 128K for read only resources
2018-05-22 Fixed airwires
2018-05-22 enbiggened the trace from the lipo
2018-05-23 Always RUN DRC
2018-05-24 moved uart task to a cpp Task
2018-05-25 command handler added
2018-05-27 Initial demo using the CPP BLE Stack with max data usage.
    Device Name: GOURRY!!!!
    Manufacturer Data: EGGPLANTS
2018-05-27 start of bluetooth command structure, implement updating advertised badge name and manufacturer data
2018-05-27 Dc26 badge to badge (#27)
    * Initial demo using the CPP BLE Stack with max data usage.
    Device Name: GOURRY!!!!
    Manufacturer Data: EGGPLANTS
    * start of bluetooth command structure, implement updating advertised badge name and manufacturer data
2018-05-27 Convert BLE to Task and add .init() fix for command_handler
2018-05-28 flash handling updated for stm32f411 proc
2018-05-28 BT: Start of badge-to-badge comms
2018-05-29 sdkconfig
2018-05-29 nearly all setup
2018-05-29 restructuring. non-functional at the moment
2018-05-30 adding new commands so we can start to test creating a ap then stopping it
2018-05-30 one way comms, i think the tasks are preventing preemption and therefore message delivery, will convert to no tasks at all
2018-05-31 progress, but still failing to receive a notification.
2018-05-31 basic two-way communications. Time to start defining interactions.
2018-06-01 realized there is already a message type so removed the redundant one added a message instance id added switch statement in uart handler to seed the code that will route messages
2018-06-02 testing queues, does not work, xQueueReceive never returns true, despite xQueueSendFromISR successfully placing the item on the queue
2018-06-03 set current state in init
2018-06-03 dding pics
2018-06-03 removed vin from esp and stm32 programer headers you will need to have battery connected to program
2018-06-03 check # messages waiting
2018-06-05 start of security stuff. Fix a bug with pure-virtual destructor in BLESecurity.h. Super annoying
2018-06-05 adding real data sheet for switch
2018-06-06 interaction diagram
2018-06-06 start of security / bluetooth pairing
2018-06-13 basic serialization complete
2018-06-17 security messages
2018-06-17 basics of sd card working still have work todo to get flatbuffers working Buttons now working
2018-06-18 Old pairings are stored in NVS. This means all subsequent connections WILL NOT require verification. For testing, i've erased NVS on each boot, so that the keys will always be passed
2018-06-18 clean up and make it a bit quieter on boot
2018-06-18 Dc26 badge to badge (#28)
    * Initial demo using the CPP BLE Stack with max data usage.
    Device Name: GOURRY!!!!
    Manufacturer Data: EGGPLANTS
    * start of bluetooth command structure, implement updating advertised badge name and manufacturer data
    * Convert BLE to Task and add .init() fix for command_handler
    * Add passive and active scanning. Also apparently pairing works auto-magically!
2018-06-18 fixed flatbuffer serialization in test code
2018-06-19 game of life now works with any size rather than limited to 32 width
2018-06-22 3d render working
2018-06-28 breakout some characteristics we expect to use, and start an interface to set/read them
2018-07-02 reduce features of server out characteristics so that notifications work properly
2018-07-03 serial carve-out. builds but not tested
2018-07-08 added esp test
2018-07-08 mcu to mcu chatter works proven by passing system info from esp to stm
2018-07-08 added new menu states stubbed messages for pairing
2018-07-11 closer...
2018-07-13 works for 1 message, still need to clean up buffers so you can fetch 2+ messagesy
2018-07-13 1 message can go from stm to esp then esp to stm
2018-07-13 Game of life mcuto mcu (#31)
    * need to test mcu to mcu communication
    basic game of life working again
    * game of life now works with any size rather than limited to 32 width
    * 3d render working
    * wip
    * updated to latest firmware
2018-07-14 line endings
2018-07-14 start of final API re-format. NOT TESTED, PROBABLY DOESN'T COMPILE
2018-07-15 as long as the ESP is boot after the STM things work
2018-07-15 flatbuffer updates for ble. Does not build, do not merge to master. Can't build flatbuffers on linux at the moment
2018-07-15 flatbuffers built, esp builds. NOT TESTED, WILL ALMOST CERTAINLY CRASH
2018-07-15 parse all STM->ESP messages and breakout their arguments for each function. Next: implement each function and test
2018-07-15 broken test, not sure i'm creating the flatbuffer correctly
2018-07-15 broken creation of a Message object, not sure how to fix
2018-07-16 fixing line endings
2018-07-16 line ending
2018-07-16 working message build
2018-07-16 merging lastest from dc26 badge to badge
2018-07-16 fixing compile errors in ble y
2018-07-16 Commsetting class abou 1/2 done
2018-07-17 move filter enum to common, re-generated files, add exposure stubs
2018-07-17 add getQueue function to BLETask
2018-07-17 Added board design files and code for Eggplant SAO
2018-07-18 return values for all the simple stuff
2018-07-18 started IO, question - can the data we are sending contain NULL bytes? Or can we format into ASCII before sending to avoid this?
2018-07-18 IO Working, GOURRY OUT
2018-07-18 io testing. no secondary callback layers, those queues were remoted. One problem: 20 byte limit per notification. Send multiple?
2018-07-18 enable 27 byte messages. going. to. sleep. now. i. swear.
2018-07-20 communication ap stm just about done
2018-07-20 updates to start to handle
2018-07-22 wifi moved to command handler
2018-07-22 merged
2018-07-22 updated processMessage with BLE messages, updated command handler CommunicationStatusRequest with info for bluetooth, commented out test data, and set up all the responses for everything bluetooth ex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
2018-07-22 adding debugging
2018-07-23 wifi, ble settings now work
2018-07-23 display pairing integer on the screen
2018-07-23 added new display task
2018-07-23 adding badgeGen
2018-07-23 programmer moved
2018-07-23 convert to using DisplayTask, get rid of some pointless messages
2018-07-25 comment out a queue send
2018-07-25 basics of scan wifi in
2018-07-25 adding fonts
2018-07-25 make mid consistent and fixed a bug with entry of BLE name
2018-07-27 mcu to mcu MUCH better now
2018-07-27 initial code for scan
2018-07-27 removing test code
2018-07-28 fixed another mcu to mcu bug, scanning for NPCs now works
2018-07-28 logos didn't really work
2018-07-29 badge flashing now works as saving to flash works
2018-07-29 fixing ssd1306 height
2018-07-29 fixed mem leak in i2c code
2018-07-29 Start some progress on the badge pairing code. Should be able to send request to scan, and receive, but not parsing the receive message. Also not handling a timeout at the moment.
2018-07-30 start of badge pairing menu. Scans and finds a thing, but fails to display
2018-07-30 debugging list display code
2018-07-30 screen saver time
2018-07-30 removing jpeg lib to free up space
2018-08-01 badges can connect to one another. Server side must be in receive pairing menu for it to work.
2018-08-02 hopefully have ping/pong/ping/pong done within the pairing context
2018-08-02 simplified a bit, but still freezing after receiving first message from Alice
2018-08-02 simplify further, one last try at a fix
2018-08-02 try one last time with short message, but nope, that didn't work either, ugh
2018-08-03 THEY BOOP. THEY BOOP. THEY. BOOP.
2018-08-03 work on infections over BLE
2018-08-03 start of badge to badge infections over ble. badge is freezing again for some reason.
2018-08-04 fixed display of logos, most of code needed for npc interaction
2018-08-04 updated stickers logo
2018-08-04 all logos now show
2018-08-04 pairing all occurs in one menu
2018-08-04 forcibly stop scanning if we're the server receiving a security request before we request a pin confirmation. This kills the gourry.
2018-08-05 change device name when agent changes their name or when they change the advertised name.
2018-08-05 egg plant working
2018-08-05 stm pairing is stable now, but the ESP still crashes if people try to pair a second time. nvs_flash_erase has been put back in place for ESP reboot to help this.
2018-08-05 bigger font. don't merge this i'm not convinced it's not causing the esp crash problem
2018-08-06 NPC interactions nearly working...however I did notice the web server may not be working any more
2018-08-06 no longer erase nvs flash
2018-08-06 basics of npc interact are in
2018-08-06 npc interactions over wifi...done
2018-08-06 adding program both shell
2018-08-07 npc bssid filter in place must start with 0xdcd
2018-08-07 use the lower screen to display things
2018-08-07 slim down messaging
2018-08-07 show exposure data in make monitor
2018-08-07 fixed initialize of infections
2018-08-07 fixed displays fixed delay on npc interact
2018-08-07 correct infection bits over adverts
2018-08-07 attempt to utilize nvs flash
2018-08-07 commit nvs to successfully write
2018-08-07 only scan once every 3 minutes
2018-08-07 added gater's index file
2018-08-07 added code to connect with phone and display messages typed with phone on the esp display
2018-08-07 add serial booping
2018-08-08 uber user badge pushes Operative name to any user they pair with and displays it on their screen
2018-08-10 ESP now have some cool messages, and web server works again this was done by right sizing memory for each task
2018-08-11 paritial fix for ble
